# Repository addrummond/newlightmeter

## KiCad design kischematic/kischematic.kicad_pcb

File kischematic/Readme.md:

PChan MOSFET http://www.mouser.co.uk/ProductDetail/ROHM-Semiconductor/RZM001P02T2L/?qs=sGAEpiMZZMshyDBzk1%2fWi5brl1xcCtmLC2Mq%252brqhxE4aWyoIiu38IQ%3d%3d
NChan http://www.mouser.co.uk/ProductDetail/ROHM-Semiconductor/RE1C002UNTCL/?qs=sGAEpiMZZMshyDBzk1%2fWi5brl1xcCtmLX9T5kEFqBHnWEMk%2fgV3G4w%3d%3d

Low freq crystal: NX3215SA
High (16MHz) freq crystal: NX3225SA

USB-C connector protrusion above top layer: 0.475
USB-C connector protrusion above bottom layer: 2.265
USB-C total height: 3.34

EFM32 height: 0.85
BlueNRG-MS height: 0.85
BQ2971 height: 0.8
MMA8653FC height: 1.0
APDS-9303 height: 0.55
TPS62230: 0.65
Skyworks thing: 0.75
Inductor height: 1.0
Antenna height: 1.07
Dual MOSFET height: 0.9
EZMate thing: 1.4
Screen: 1.45
Zif connector height: 2
Low freq crystal: 0.9
High freq crystal: 0.55

Newest pair of crystals (available on Mouser):
http://www.mouser.co.uk/Search/ProductDetail.aspx?R=ECS-.327-12.5-34B-TRvirtualkey59070000virtualkey520-327-12.5-34B
http://www.mouser.co.uk/Search/ProductDetail.aspx?R=ECS-160-8-30B-CKMvirtualkey59070000virtualkey520-160-8-30B-CKM

Magic micro:

http://www.silabs.com/support%20documents/technicaldocs/efm32hg309.pdf

Suitable flat flex cable (cut in half):

http://www.digikey.co.uk/product-detail/en/molex-llc/0152660073/WM11348-ND/3160809

Side mount switch:

http://uk.rs-online.com/web/p/products/7856443/?grossPrice=Y&cm_mmc=UK-PLA-_-google-_-PLA_UK_EN_Switches-_-Tactile_Switches_And_Accessories&mkwid=slV9EyTsH_dc|pcrid|88057077243|pkw||pmt||prd|7856443&gclid=Cj0KEQiAnIPDBRC7t5zJs4uQu5UBEiQA7u5Nez5Wsqkz7oU2pIy9AWAJCai1eRbfQIoq8IcizyYJO9QaAkB28P8HAQ

Useful info on EFM32 3-wire SPI:

http://community.silabs.com/t5/32-bit-MCU-Knowledge-Base/EFM32-as-a-3-wire-SPI-master/ta-p/123022

New dual MOSFET:

http://www2.mouser.com/ProductDetail/Infineon-Technologies/BSD840NH6327XTSA1/?qs=sGAEpiMZZMshyDBzk1%2fWi4lI00SCTc04GvAMPB9W6%252bI%3d

New buck:

http://www2.mouser.com/ProductDetail/Texas-Instruments/TPS62237DRYR/?qs=sGAEpiMZZMtitjHzVIkrqbYrYgRelM8b2WQIr2d%2f%2fYU%3d

Low profile shileded inductor (1.0mm):

http://www2.mouser.com/ProductDetail/Bourns/SRP2010-1R0M/?qs=sGAEpiMZZMsg%252by3WlYCkU8UvYHBUd1aBW8CnykdJK88%3d

Old shielded inductor:

http://www2.mouser.com/ProductDetail/Sumida/CDRH2D18-HPNP-100NC/?qs=sGAEpiMZZMsg%252by3WlYCkU%252bh%252bN6dP7ETY7aXNPTXOGEY%3d
http://www.mouser.com/ds/2/390/cdrh2d18hp-339282.pdf

Old buck:

http://www2.mouser.com/ProductDetail/Texas-Instruments/LM3670MF-33-NOPB/?qs=sGAEpiMZZMtitjHzVIkrqaeIqJaO9bXJbUmg3vjvnY4%3d

USB-C midmount connector:

http://www.farnell.com/cad/1993947.pdf?_ga=1.47058095.988751352.1481488664

Notes on USB C configuration:

https://www.scorpia.co.uk/2016/03/17/using-usb-type-c-on-hobyist-projects/

3.2V LDO:

http://www2.mouser.com/ProductDetail/ROHM-Semiconductor/BU32TD3WG-TR/?qs=sGAEpiMZZMsGz1a6aV8DcPH%252bYFoKpp%252bQXAL4Sdb5MQA%3d

Little pogo pins:

http://www.digikey.co.uk/product-detail/en/mill-max-manufacturing-corp/0921-1-15-20-75-14-11-0/ED1655-ND/2784010

Trace impedance calc:

http://emclab.mst.edu/pcbtlc2/microstrip/

Trace thickness: 0.03556
Relative permittivity: 4.8

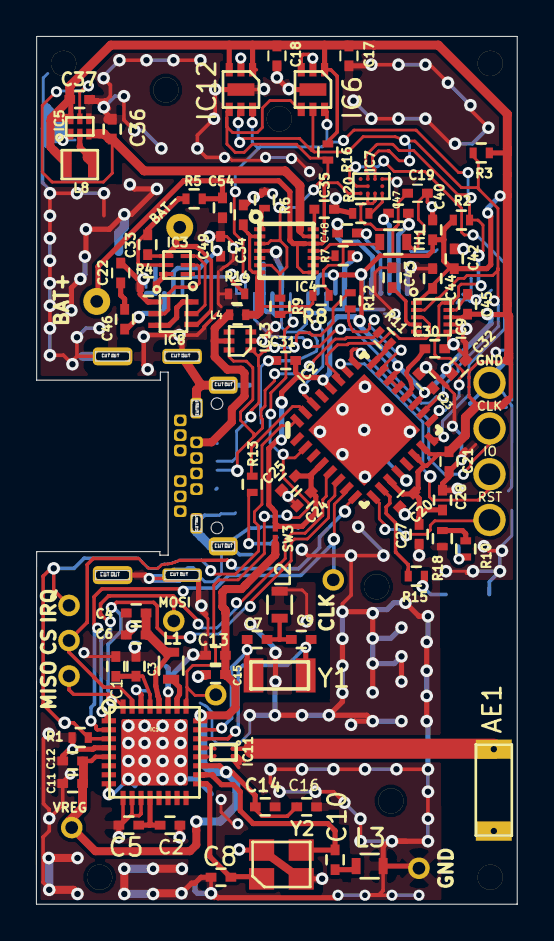
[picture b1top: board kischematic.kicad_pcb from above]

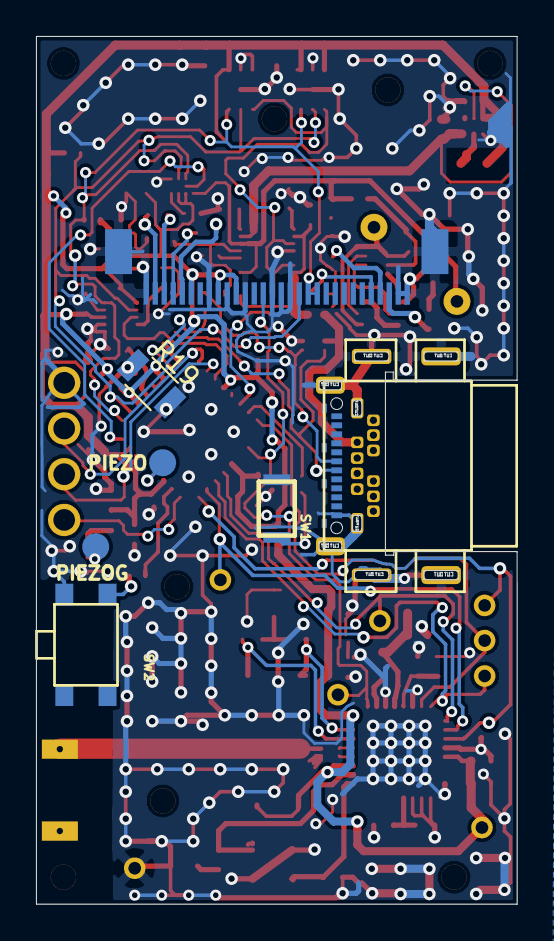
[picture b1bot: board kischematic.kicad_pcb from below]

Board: 2 copper layers, 26.7 x 48.2 mm, 111 parts (7 on the bottom side), 65 nets.

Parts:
AE1: Antenna_Dipole; AN2051
C1, C2: BY100p; C_0402
C3: BY150n; C_0402
C4, C11, C13, C16: BY1u; C_0402
C5, C6, C12, C14, C15: BYu1; C_0402
C7, C9: HP22p; C_0402
C8, C10: HP15p; C_0402
C17, C18, C19, C20, C24, C31, C33, C35, C43, C44, C45: u1; C_0402
C21, C27: 10n; C_0402
C22, C37, C46: DC-DC 4u7; C_0402
C23: X5R 4u7; C_0402
C25, C28, C34, C54: 10u; C_0402
C30, C42: 1u; C_0402
C32: X5R u1; C_0402
C36, C49: BY 4u7; C_0402
C40, C47, C48: DC-DC 1u; C_0402
IC1: BlueNRG; QFN32
IC2: EFM32HG310; EMFQFN_32
IC3: BQ297xx; WSON6
IC4: AAT3672IWO-4.2-1; AAT3672IWO
IC5: TPS6223xx
IC6, IC12: MAX44009
IC7: STC3115; STC3115IJT
IC8: BSD840NH6327XTSA1; SOT-363
IC9: MMA8653FC; DFN10
IC10: 128x64OLED; ER-OLED096-1
IC11: BALF-NRG-01D3
IC13: USBLC6-4; SOT-666
J1, J2, J3, J4, J5, J6, J7, J8: Screw_Terminal_1x01; M1.4MOUNTHOLE
L1: DC-DC 4u7; R_0603
L2, L3: 3n9; R_0603
L4: 33; R_0402
L8: DC-DC 1u; SRP2010
P1, P2, P3, P4, P5, P6, P7, P8: CONN_01X01; WIREPAD
R1, R8, R16: 10k; R_0402
R2, R3, R10, R13, R15, R18: 1k; R_0402
R4: 2k2%; R_0402
R5: 330%; R_0402
R6: 2M7%; R_0402
R7: 1M6%; R_0402
R9, R11, R12: 15R; R_0402
R14: 91k%; R_0402
R19: 1k; R_1206
R20: 50m%; R_0402
SW1: SW_Push; KXT131LHS
SW2: SW_Push; 434333045822
SW3: SW_DIP_x01; PWRJUMPER
TH1: 10k; R_0603
TP1, TP2, TP3, TP4: TEST; SMALLWIREPAD
U1: USB-C; 2129691-1
U2: SWD_SPRING
Y1: 32k; CRYSTAL3.2x1.5mm
Y2: 16M; CRYSTAL2.2x1.6

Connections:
ACCELINT1: IC2.27, IC9.3
ANT: AE1.1, IC11.1
BAT+: C54.1, IC4.8, IC4.12, IC7.A3, R5.2
BAT-: C33.1, IC3.4, IC8.4
BATD: IC2.16, IC7.B2
BNRG_SPI_CS: IC1.31, IC2.8, P5.1
BNRG_SPI_IRQ: IC1.3, IC2.32, P6.1, R1.1
DISPLAY_RESET: IC1.25, IC2.2, IC10.14, P8.1
EFMRESET: IC2.9, U2.1
GND: C1.1, C2.2, C3.1, C4.1, C5.2, C6.1, C8.2, C11.2, C12.2, C13.1, C14.2, C15.1, C16.2, C17.2, C18.2, C19.2, C20.1, C21.1, C22.1, C23.1, C24.2, C25.2, C27.1, C28.2, C30.1, C31.1, C32.1, C34.1, C35.1, C36.2, C37.1, C40.2, C42.2, C43.1, C44.2, C45.1, C49.1, C54.2, IC1.0, IC1.4, IC1.8, IC1.9, IC1.10, IC1.11, IC1.27, IC1.30, IC2.33, IC4.4, IC5.1, IC5.4, IC6.2, IC6.3, IC6.7, IC7.D1, IC8.1, IC9.6, IC9.7, IC9.9, IC10.1, IC10.8, IC10.10, IC10.12, IC10.15, IC10.16, IC10.17, IC10.29, IC10.30, IC10.31, IC10.32, IC11.2, IC12.2, IC12.7, IC13.2, L2.1, L3.2, P7.1, R1.2, R4.1, R6.1, R7.1, R14.2, R18.2, R19.1, R19.2, R20.2, SW1.2, SW2.2, TH1.1, U1.A1, U1.B1, U1.B12, U1.S1, U1.S2, U1.S3, U1.S4, U1.S5, U1.S6, U2.4, Y2.2, Y2.3
I2C_SCL: IC2.18, IC6.5, IC7.C1, IC9.2, IC10.18, IC12.5, R3.2
I2C_SDA: IC2.17, IC6.6, IC7.B1, IC9.10, IC10.19, IC10.20, IC12.6, R2.2
MAINBUTTON: IC2.31, R13.2
unnamed: C1.2, C3.2, IC1.29
unnamed: C2.1, C5.1, IC1.12
unnamed: C4.2, C6.2, IC1.28, L1.1
unnamed: C7.1, C9.1, L2.2
unnamed: C7.2, IC1.23, Y1.1
unnamed: C8.1, IC1.17, Y2.1
unnamed: C9.2, IC1.22, Y1.2
unnamed: C10.1, IC1.18, Y2.4
unnamed: C10.2, L3.1
unnamed: C22.2, C46.1
unnamed: C30.2, IC2.20
unnamed: C33.2, IC3.5, R5.1
unnamed: C35.2, IC4.14
unnamed: C43.2, IC9.4
unnamed: C46.2, IC10.28
unnamed: C47.1, IC10.3
unnamed: C47.2, IC10.2
unnamed: C48.1, IC10.5
unnamed: C48.2, IC10.4
unnamed: C49.2, IC10.27
unnamed: IC1.20, IC11.3
unnamed: IC1.21, IC11.4
unnamed: IC1.26, L1.2
unnamed: IC2.24, R11.1
unnamed: IC3.2, IC8.2
unnamed: IC3.3, IC8.5
unnamed: IC3.6, R4.2
unnamed: IC4.1, R6.2
unnamed: IC4.10, R7.2
unnamed: IC4.11, R8.2, TH1.2
unnamed: IC5.2, L8.1
unnamed: IC7.D3, R20.1
unnamed: IC8.3, IC8.6
unnamed: IC10.26, R14.1
unnamed: R10.2, R18.1
unnamed: R13.1, SW1.1
unnamed: R15.1, SW2.1
PSTAT1: IC2.30, R9.1
PSTAT1X: IC4.3, IC4.6, IC6.4, IC12.4, R9.2, R16.1
SECONDBUTTON: IC2.10, R15.2
SPI_CLK: IC1.2, IC2.7, P2.1
SPI_MISO: IC1.32, IC2.6, P3.1
SPI_MOSI: IC1.1, IC2.5, P4.1
SWCLK: IC2.25, U2.3
SWDIO: IC2.26, U2.2
USBD+: IC13.6, R11.2, U1.A6
USBD-: IC13.1, R12.2, U1.A7
USBD-BR: IC2.23, R12.1
VLOAD: C36.1, IC4.13, IC5.3, IC5.5
VREG: C11.1, C12.1, C13.2, C14.1, C15.2, C16.1, C17.1, C18.1, C19.1, C20.2, C21.2, C23.2, C24.1, C25.1, C27.2, C28.1, C31.2, C32.2, C37.2, C40.1, C42.1, C44.1, C45.2, IC1.5, IC1.19, IC1.24, IC2.4, IC2.11, IC2.14, IC2.15, IC2.19, IC2.21, IC2.22, IC2.28, IC5.6, IC6.1, IC7.B3, IC7.C3, IC9.1, IC9.8, IC10.6, IC10.9, IC10.11, IC12.1, IC12.3, L8.2, P1.1, R2.1, R3.1, R16.2, SW3.1, SW3.2
VUSB: C34.2, IC4.2, IC4.7, L4.1, R8.1
VUSB_B4F: IC13.5, L4.2, U1.B4

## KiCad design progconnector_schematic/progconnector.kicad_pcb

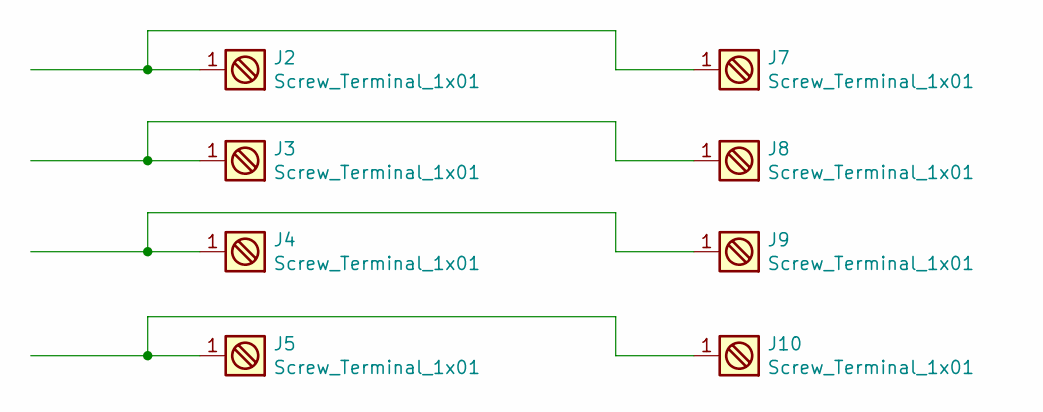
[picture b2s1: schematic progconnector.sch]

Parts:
J2, J3, J4, J5: Screw_Terminal_1x01; Pin_Header_Straight_1x01_Pitch2.54mm
J7, J8, J9, J10: Screw_Terminal_1x01; POGOHOLDER

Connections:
unnamed: J2.1, J7.1
unnamed: J3.1, J8.1
unnamed: J4.1, J9.1
unnamed: J5.1, J10.1

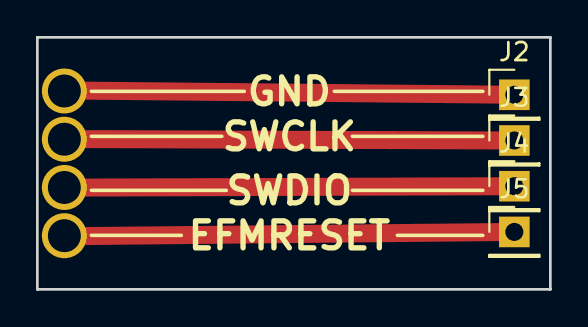
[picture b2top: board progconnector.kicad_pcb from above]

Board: 2 copper layers, 28.5 x 14.0 mm, 8 parts (0 on the bottom side), 4 nets.

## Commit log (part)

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2017-02-09 Minor.
2017-02-09 Add SOT-416FL footprint.
2017-02-09 Some initial tearing down.
2017-02-10 Update schematic for EFM32HG310
2017-02-10 Add footprints.
2017-02-10 Initial update of pcb with new components.
2017-02-10 Lots of tearing down.
2017-02-10 More tearing down and moving.
2017-02-10 Some initial routing work.
2017-02-10 More routing work.
2017-02-10 More insane routing.
2017-02-10 More crazy routing.
2017-02-10 More insane routing work.
2017-02-11 More insane routing, including idea of linking CHENABLE and PSTAT1
2017-02-11 Add hole for mouting sensor cover.
2017-02-11 Tweaks.
2017-02-11 Majority of difficult routing now done.
2017-02-11 Some initial work on programming connector adapter thing.
2017-02-11 More routing / pogo work.
2017-02-11 Make board slightly shorter.
2017-02-11 Initial work on making space for usb diodes.
2017-02-11 More routing.
2017-02-11 Some tweaks to silkscreen.
2017-02-11 More work on silkscreen.
2017-02-12 More tweaks.
2017-02-12 Add another mounting hole.
2017-02-12 Add missing track.
2017-02-12 Fix DRC/ERC errors and some other tweaks.
2017-02-12 DRC/ERC fixes; bring 100 BlueNRG DC-DC cap closer to chip.
2017-02-12 Add jumper connecting BlueNRG power to rest of board.
2017-02-12 Some improvements to GND connectivity.
2017-02-12 Get rid of 2u2 caps.
2017-02-12 Replace single 2k2 piezo resistor with two 1k resitors.
2017-02-13 Messing around with firmware.
2017-02-13 Some tweaks to main.c; add constants in accel.h
2017-02-13 Some work on bat positioning.
2017-02-14 Move main button up a bit.
2017-02-14 Move main button up a bit further.
2017-02-16 Add possibly usefuly hole to help with mounting center button.
2017-02-18 Correct screw hole sizes.
2017-02-18 Remove dead track.
2017-02-19 Some imporvements to VREG routing to display.
2017-02-27 Fix DRC errors.
2017-02-28 Add GND jumper.
2017-03-01 Work on programming connector board.
2017-03-03 New stratey for programming connector (jam pin header in).
2017-03-03 Minor.,
2017-03-04 DRC fix.
2017-03-06 Route light sensor interrupt.
2017-03-06 Add some notes on X5R
2017-03-06 Move USB termination resistor closer to EFM32.
2017-03-06 Add ferrite bead for VUSB.
2017-03-06 Move SPI_IRQ wire pad.
2017-03-07 More tweaking.
2017-03-07 Silk tweaks.
2017-03-07 DRC fixes.
2017-03-07 Move resistor further from USB connector.
2017-03-07 Tweaks to balun layout.
2017-03-07 Tweak to ANT trace thickness.
2017-03-07 Move resistor further from BAT- wire pad.
2017-03-07 Tidy up silk screen.
2017-03-07 Minor; probably next board.
2017-03-07 Very minor changes.
2017-03-07 Add gerbers for second pcbway order.
2017-03-07 Increase all USB connector plated slots to 0.5mm.
2017-03-07 Add gerbers for revision 2 of pcbway order 2
2017-03-13 Some preliminary work on diffuser simulation
2017-03-14 More QTree work.
2017-03-14 More work on QTree.
2017-03-14 Some initial work on initializing graphics.
2017-03-14 More graphics work.
2017-03-14 More work on graphics.
2017-03-14 More work on grahpics.
2017-03-14 some work on QTree iterator.
2017-03-16 Lots of bug fixes.
2017-03-16 More work on QTrees.
2017-03-16 Some work on prettier rendering to help with debugging.
2017-03-16 Reorganize QTree code to make it more generic.
2017-03-16 Some work on optimal quadtree construction -- not there yet.
2017-03-16 Significant progress on constructing better QTrees.
2017-03-16 Some initial work on ray tracing code.
2017-03-16 Reorganize code for walking through QTree to use iterators.
2017-03-16 Tweak to ray tracing iter.
2017-03-16 More work on ray tracing.
2017-03-16 Computation of ray/segment intersection with aid of QTree now basically working.
2017-03-17 Some initial work on geom_import.rs
2017-03-17 Parsing code now working a bit.
2017-03-18 Simple parser using nom parser combinator library now working.
2017-03-18 Parsing now basically working.
2017-03-18 Some initial steps at using hand-writted rec descent parser instead of nom
2017-03-18 Rec descent parser now basically working.
2017-03-18 Finishing touches to geom parser.
2017-03-18 Add test.geom file.
2017-03-19 Lots of improvements to geom code.
2017-03-19 Some initial work on ray tracing stuff.
2017-03-19 Lots of bug fixes to geometry code; more preliminary ray tracting work.
2017-03-19 Further fixes to ray tracing code and geom import code.
2017-03-20 Some initial work on switching to SVG output.
2017-03-20 More work on svg out.
2017-03-20 Minor bug fix.
2017-03-20 TODO
2017-03-21 Major bug fixes to diffuse reflection calculations.
2017-03-22 Some bad code for lightening rays as they get weaker.
2017-03-23 Code for calculating reflected rays now working.
2017-03-23 Some refactoring in geom.rs
2017-03-23 More refactoring; depth-first rather than breadth-first tracing.
2017-03-23 Remove random mistake.
2017-03-23 Some initial work on refraction stuff.
2017-03-23 Some initial work on refraction.
2017-03-27 Various bug fixes.
2017-03-27 Add support for comments in geometry file.
2017-03-27 Switch back to depth first.
2017-03-27 Fix to comment parsing in geom_import.rs
2017-03-27 Add support for refraction.
2017-03-28 Some initial work on adding beams to geom import.
2017-03-28 More work on rays in geom input file.
2017-03-28 Minor fix to geom import parser.
2017-04-03 Various improvements to geom import; allow specifications of beams
2017-04-03 Minor refactoring to use is_digit in geom_import.rs
2017-04-03 Remove buggy and unused node counting logic for QTrees.
2017-04-07 Add support for specifying arcs in geom file.
2017-04-07 Couple of minor corrections to geom parser.
2017-04-07 Remove some compiler warnings.
2017-04-07 Fix bugs in arc_to_segments caused by accidental use of 'cos' instead of 'acos'
2017-04-07 Remove variable defs left over from debug logging in geom.rs.
2017-04-07 Some more work on arcs.
2017-04-07 Update arc to segs code to handle circles properly.
2017-04-07 Fix some bugs with construction of arc geometry in geom_import.rs
2017-04-07 Various improvements to rendering.
2017-04-07 Some intitial work on making it possible to name segments.
2017-04-07 Some code style improvements to geom_import.rs
2017-04-07 Some initial work for logging.
2017-04-07 Refactoring: move some code from geom.rs into new file trace.rs
2017-04-10 Some significant refactoring of QTree code in geom.rs
2017-04-10 Fix typo in comment in geom.rs
2017-04-10 Remove some unnecessary 'return' statements in geom.rs.
2017-04-11 Add some comments on nasty borrow stuff to geom.rs.
2017-04-14 Add 'circle' convenience command in geom import syntax.
2017-04-14 Improve code for choosing new center points in geom.rs
2017-04-15 Minor refactoring.
2017-04-16 Lots of refactoring; initial work on event triggering.
2017-04-16 Event logging now basically working.
2017-04-16 Fix runtime error when segments vector is empty.
2017-04-16 Remove some logging in main.rs
2017-04-16 Fix arc construction code in geom.rs.
2017-04-16 Extra options for 'arc' in geom import; fix some general parser bugs.
2017-04-16 Some refactoring and code style changes in geom_import.rs
2017-04-16 For some reason I thought that the Rust stdlib doesn't have is_digit; it does
2017-04-17 Refactor parser to read bytes directly rather than decoded strings.
2017-04-17 Add support for 'ray' as well as 'beam' decl in parser.
2017-04-17 Detect duplicate segment names in parser.
2017-04-17 Some improvements to parser error reporting and minor bug fixes.
2017-04-17 Some refactoring.
2017-04-17 Split parser combinator stuff out into separate module.
2017-04-17 Some further refactoring of parser.
2017-04-17 Minor tweaks to parsing code.
2017-04-18 Add code to geom_import.rs for combining multiple geom files.
2017-04-18 Some tweaks to combine_imported_geometry
2017-04-22 Lots of work on turning this into a proper command line util.
2017-04-22 Fix bug in combine_imported_geometry in geom_import.rs
2017-04-22 Allow multiple geomfile args.
2017-04-22 Fix potential array bounds error in parcombs.rs
2017-04-22 Add doc comments to parcombs.rs and make some minor tweaks to code.
2017-04-22 More parser tweaks.
2017-04-23 More work on usability of command line.
2017-04-23 Some refactoring of tracing logic.
2017-04-23 Improve argument error messages and clean up some code in app.rs a bit.
2017-04-23 Add rect shortcut to parser.
2017-04-23 Improve logic for stopping/continuing tracing and parsing args.
2017-04-25 Now successfully uses multithreading.
2017-04-25 Minor code formatting change to app.rs.
2017-07-24 Tweak to board layout.
2017-07-24 Minor change.
2017-07-24 More minor tweaks.
2017-08-01 Some tweaks to tracks on pcb
2017-08-05 Updates to rpi spi bluenrg test code.
2017-08-05 Give informative names to datasheets.
2017-08-05 Add pcb design guidelines datasheet.
2017-08-05 Minor schematic tweak.
2017-08-05 Add wire colors.
2017-08-05 Update device name.
2017-08-06 Update device name to something valid.
2017-08-06 Add some comments to test.c
2017-08-06 Code reorganization.
2017-08-06 Add comment to test.c
2017-08-06 Update Readme.md for BlueNRG test build on rpi
2017-08-06 Tweak to timeouts.
2017-11-29 Minor ground connectivity edit.
2017-11-29 Make board and schematic properly consistent again.
